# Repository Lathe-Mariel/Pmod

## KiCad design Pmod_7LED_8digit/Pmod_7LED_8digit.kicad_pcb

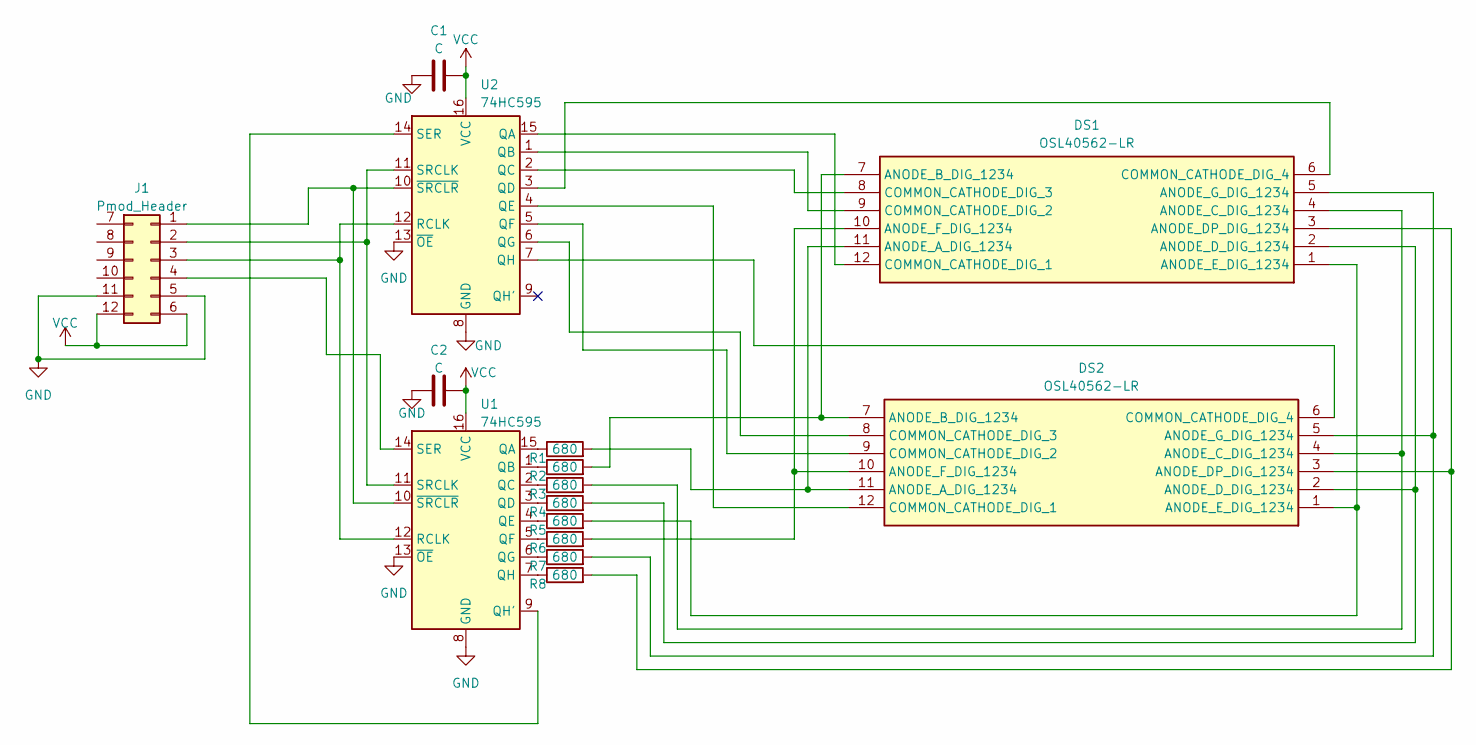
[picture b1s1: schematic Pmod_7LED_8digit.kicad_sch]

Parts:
C1: C; C_0603_1608Metric_Pad1.08x0.95mm_HandSolder
C2: C
DS1, DS2: OSL40562-LR; DIPS1524W50P254L5030H825Q12N; Manufacturer_Part_Number OSL40562-LR
J1: Pmod_Header
R1, R2, R3, R4, R5, R6, R7, R8: 680; R_0603_1608Metric_Pad0.98x0.95mm_HandSolder
U1, U2: 74HC595; SOIC-16W_5.3x10.2mm_P1.27mm

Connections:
GND: C1.2, C2.1, J1.5, J1.11, U1.8 (GND), U1.13 (~OE), U2.8 (GND), U2.13 (~OE)
unnamed: DS1.11 (ANODE_A_DIG_1234), DS2.11 (ANODE_A_DIG_1234), R1.2
unnamed: DS1.7 (ANODE_B_DIG_1234), DS2.7 (ANODE_B_DIG_1234), R2.2
unnamed: DS1.4 (ANODE_C_DIG_1234), DS2.4 (ANODE_C_DIG_1234), R3.2
unnamed: DS1.3 (ANODE_DP_DIG_1234), DS2.3 (ANODE_DP_DIG_1234), R8.2
unnamed: DS1.2 (ANODE_D_DIG_1234), DS2.2 (ANODE_D_DIG_1234), R4.2
unnamed: DS1.1 (ANODE_E_DIG_1234), DS2.1 (ANODE_E_DIG_1234), R5.2
unnamed: DS1.10 (ANODE_F_DIG_1234), DS2.10 (ANODE_F_DIG_1234), R6.2
unnamed: DS1.5 (ANODE_G_DIG_1234), DS2.5 (ANODE_G_DIG_1234), R7.2
unnamed: DS1.12 (COMMON_CATHODE_DIG_1), U2.15 (QA)
unnamed: DS1.9 (COMMON_CATHODE_DIG_2), U2.1 (QB)
unnamed: DS1.8 (COMMON_CATHODE_DIG_3), U2.2 (QC)
unnamed: DS1.6 (COMMON_CATHODE_DIG_4), U2.3 (QD)
unnamed: DS2.12 (COMMON_CATHODE_DIG_1), U2.4 (QE)
unnamed: DS2.9 (COMMON_CATHODE_DIG_2), U2.5 (QF)
unnamed: DS2.8 (COMMON_CATHODE_DIG_3), U2.6 (QG)
unnamed: DS2.6 (COMMON_CATHODE_DIG_4), U2.7 (QH)
unnamed: J1.1, U1.10 (~SRCLR), U2.10 (~SRCLR)
unnamed: J1.2, U1.11 (SRCLK), U2.11 (SRCLK)
unnamed: J1.3, U1.12 (RCLK), U2.12 (RCLK)
unnamed: J1.4, U1.14 (SER)
unnamed: R1.1, U1.15 (QA)
unnamed: R2.1, U1.1 (QB)
unnamed: R3.1, U1.2 (QC)
unnamed: R4.1, U1.3 (QD)
unnamed: R5.1, U1.4 (QE)
unnamed: R6.1, U1.5 (QF)
unnamed: R7.1, U1.6 (QG)
unnamed: U1.9 (QH'), U2.14 (SER)
unnamed: R8.1, U1.7 (QH)
VCC: C1.1, C2.2, J1.6, J1.12, U1.16 (VCC), U2.16 (VCC)

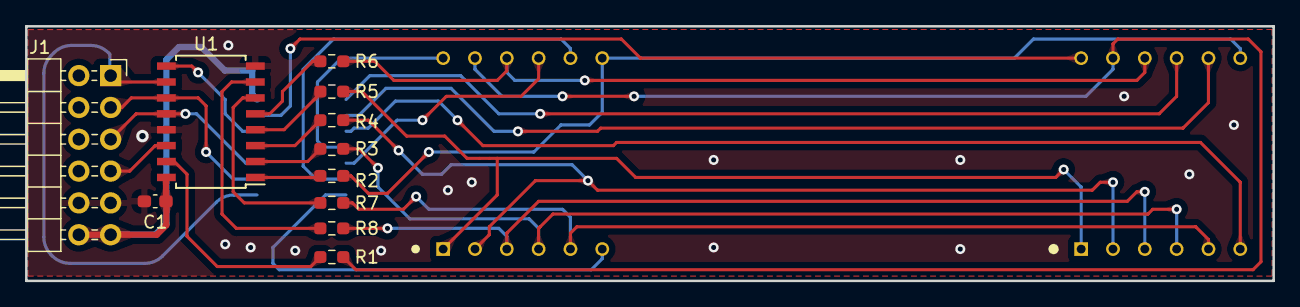
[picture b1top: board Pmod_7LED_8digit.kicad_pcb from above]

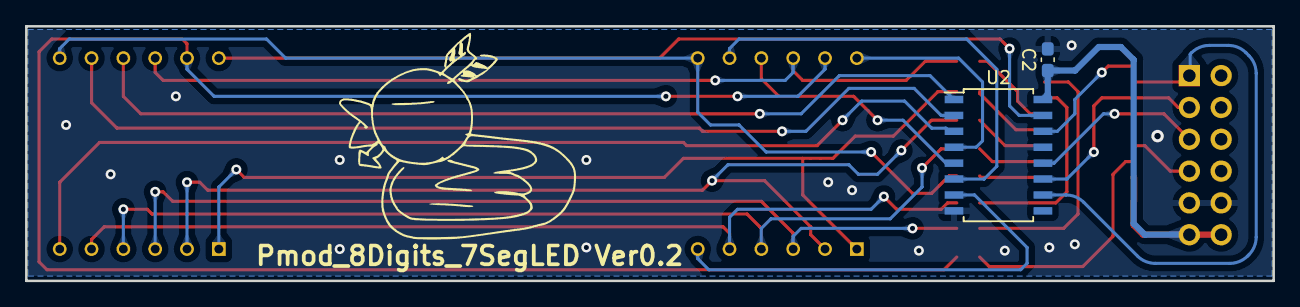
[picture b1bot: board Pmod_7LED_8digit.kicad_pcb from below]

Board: 2 copper layers, 99.6 x 20.3 mm, 15 parts (2 on the bottom side), 31 nets.

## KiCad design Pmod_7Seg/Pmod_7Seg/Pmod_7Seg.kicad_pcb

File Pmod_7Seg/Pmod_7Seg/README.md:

# Pmod_7Seg
6桁7セグLEDを載せたPmod基板．  
Pmodを2ポート使う  

2個取りした面付けデータがkikitディレクトリにあります．

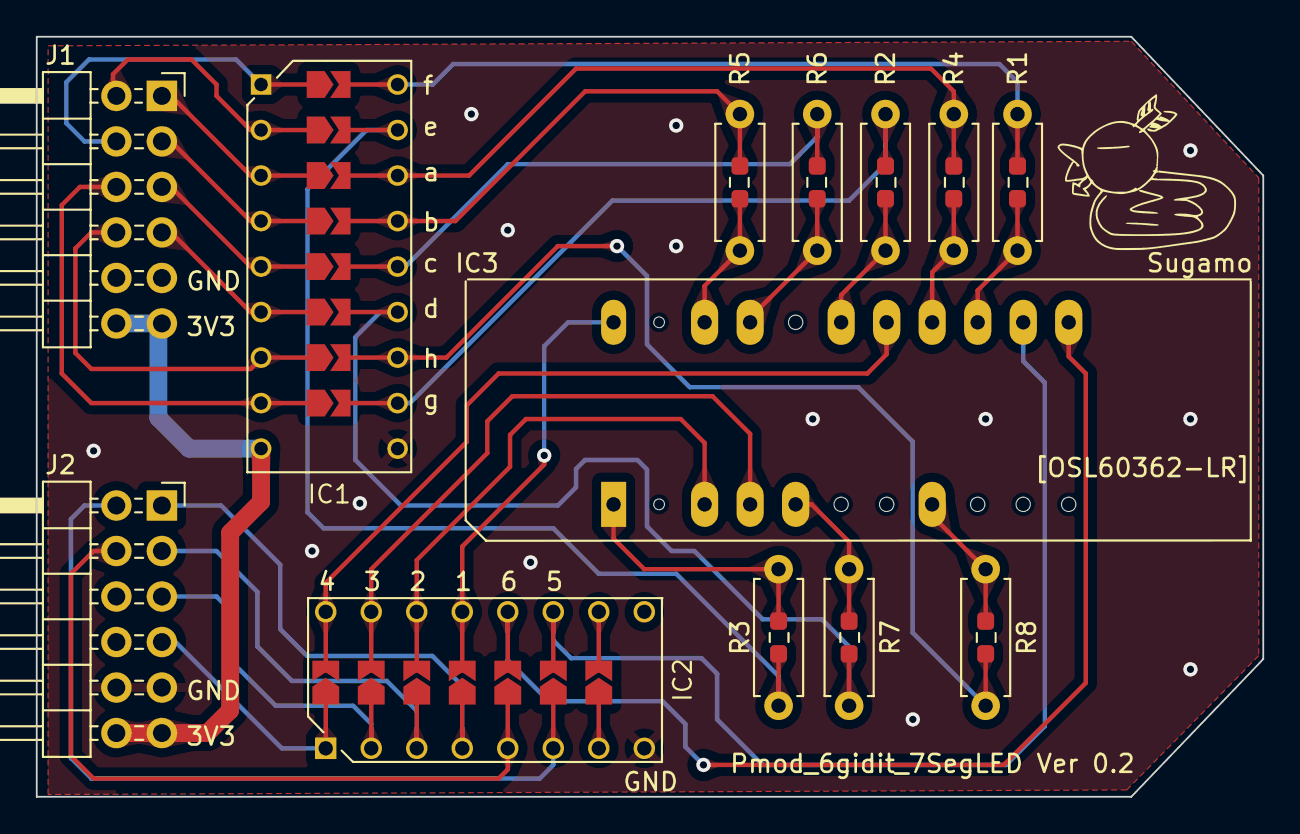
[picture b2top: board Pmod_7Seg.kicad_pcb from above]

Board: 2 copper layers, 68.5 x 42.4 mm, 13 parts (0 on the bottom side), 38 nets.

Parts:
IC1: TBD62783APG; DIP762W55P254L2286H480Q18N_with_solderjumper
IC2: TBD62003APG; DIP762W60P254L1975H445Q16N_solderjumper
IC3: OSL60362-LR; OSL60362-LR-with-allpin
J1, J2: Conn_02x06_Counter_Clockwise; Pmod
R1, R2, R3, R4, R5, R6, R7, R8: 68; Resistor_SMD_THT

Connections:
GND: IC1.10 (GND), IC2.8 (GND), J1.5, J1.11, J2.5, J2.11
unnamed: IC3.15 (ANODE_A), R4.1
unnamed: IC3.20 (ANODE_B), R5.2
unnamed: IC3.19 (ANODE_C), R6.2
unnamed: IC3.5 (ANODE_D), R7.2
unnamed: IC3.8 (ANODE_DP), R8.2
unnamed: IC3.1 (ANODE_E), R3.2
unnamed: IC3.14 (ANODE_F), R1.1
unnamed: IC3.17 (ANODE_G), R2.1
unnamed: IC2.13 (O4), IC3.22 (KATHODE_1)
unnamed: IC2.14 (O3), IC3.3 (KATHODE_2)
unnamed: IC2.15 (O2), IC3.4 (KATHODE_3)
unnamed: IC2.16 (O1), IC3.16 (KATHODE_4)
unnamed: IC2.11 (O6), IC3.13 (KATHODE_5)
unnamed: IC2.12 (O5), IC3.12 (KATHODE_6)
unnamed: IC1.1 (I1), J1.8
unnamed: IC1.2 (I2), J1.7
unnamed: IC1.3 (I3), J1.1
unnamed: IC1.4 (I4), J1.2
unnamed: IC1.5 (I5), J1.3
unnamed: IC1.6 (I6), J1.4
unnamed: IC1.7 (I7), J1.10
unnamed: IC1.8 (I8), J1.9
unnamed: IC1.18 (O1), R1.2
unnamed: IC1.17 (O2), R3.1
unnamed: IC1.16 (O3), R4.2
unnamed: IC1.15 (O4), R5.1
unnamed: IC1.14 (O5), R6.1
unnamed: IC1.13 (O6), R7.1
unnamed: IC1.12 (O7), R8.1
unnamed: IC1.11 (O8), R2.2
unnamed: IC2.4 (I4), J2.1
unnamed: IC2.3 (I3), J2.2
unnamed: IC2.2 (I2), J2.3
unnamed: IC2.1 (I1), J2.4
unnamed: IC2.6 (I6), J2.7
unnamed: IC2.5 (I5), J2.8
VCC: IC1.9 (VCC), J1.6, J1.12, J2.6, J2.12

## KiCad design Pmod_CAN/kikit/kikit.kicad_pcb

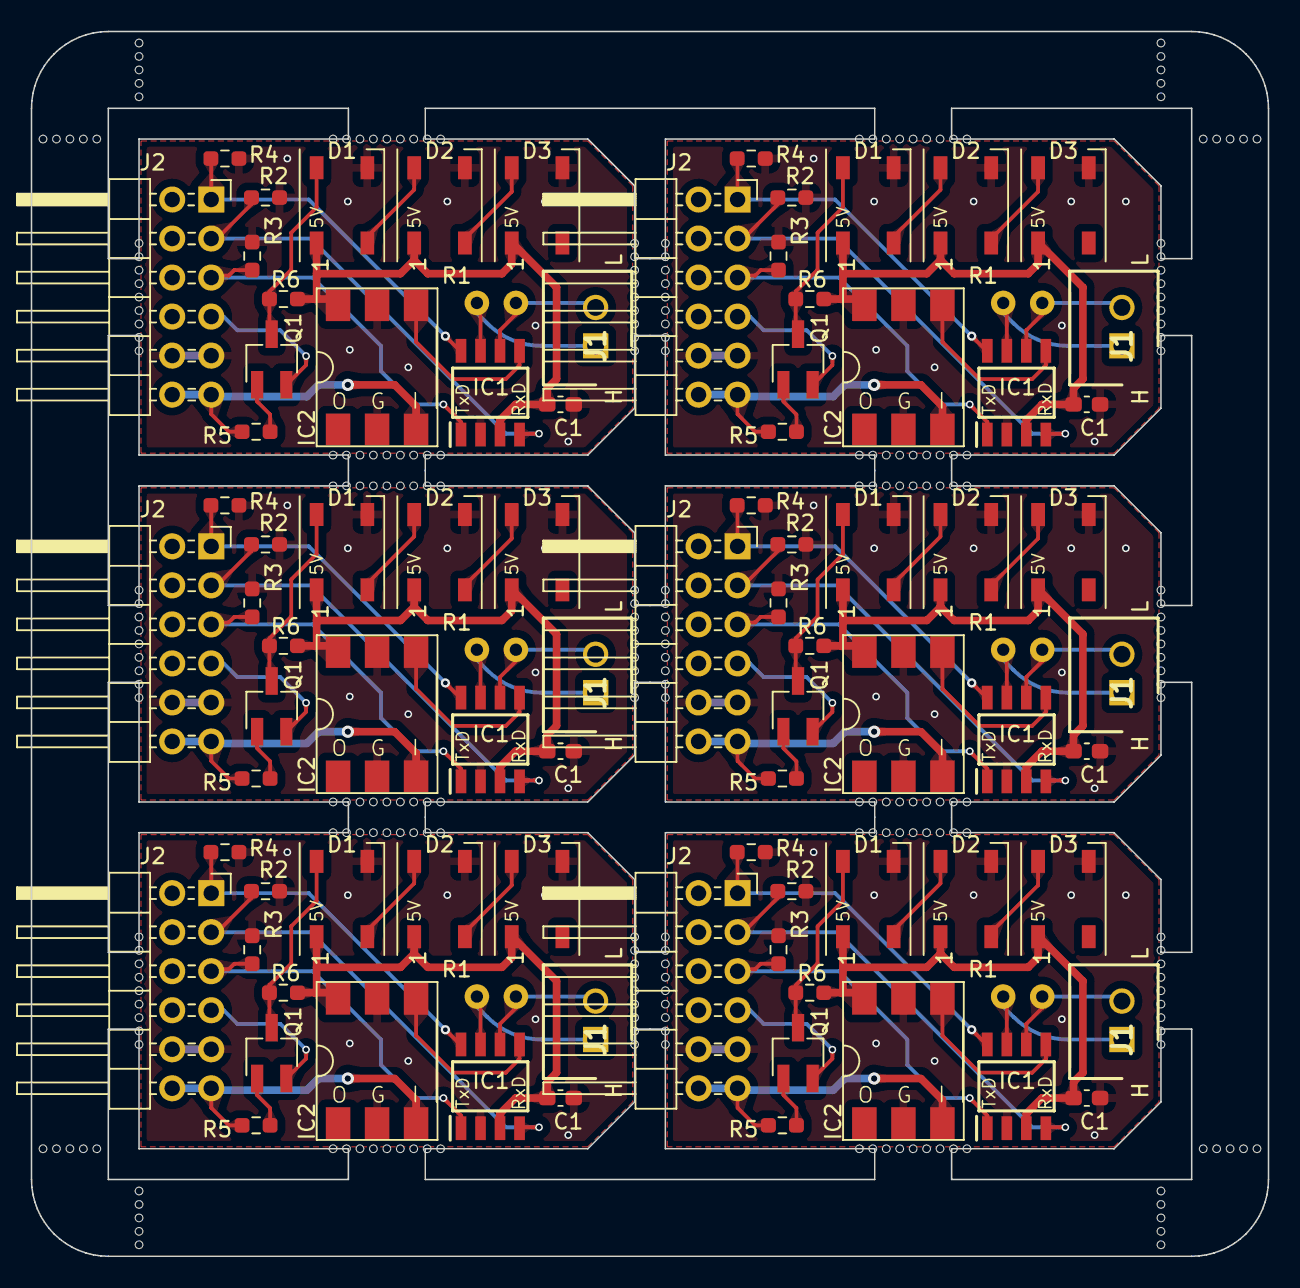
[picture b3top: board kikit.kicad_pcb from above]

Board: 2 copper layers, 80.5 x 79.7 mm, 346 parts (0 on the bottom side), 78 nets.

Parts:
C1, C1#2, C1#3, C1#4, C1#5, C1#6: 0.1u; C_0603_1608Metric_Pad1.08x0.95mm_HandSolder
D1, D1#2, D1#3, D1#4, D1#5, D1#6, D2, D2#2, D2#3, D2#4, D2#5, D2#6, D3, D3#2, D3#3, D3#4, D3#5, D3#6: WS2812B; LED_WS2812B_PLCC4_5.0x5.0mm_P3.2mm
IC1, IC1#2, IC1#3, IC1#4, IC1#5, IC1#6: TJA1441AT; SOIC127P600X175-8N
IC2, IC2#2, IC2#3, IC2#4, IC2#5, IC2#6: AE_XC9306-5V0; AE-XC9306-5V0
J1, J1#2, J1#3, J1#4, J1#5, J1#6: B2B-XH-A_LF__SN_; SHDR2W64P0X250_1X2_740X575X700P
J2, J2#2, J2#3, J2#4, J2#5, J2#6: Pmod_Header; Pmod
KiKit_MB_1_1, KiKit_MB_1_2, KiKit_MB_1_3, KiKit_MB_1_4, KiKit_MB_1_5, KiKit_MB_1_6, KiKit_MB_1_7, KiKit_MB_1_8, KiKit_MB_1_9, KiKit_MB_2_1, KiKit_MB_2_2, KiKit_MB_2_3, KiKit_MB_2_4, KiKit_MB_2_5, KiKit_MB_2_6, KiKit_MB_2_7, KiKit_MB_2_8, KiKit_MB_2_9, KiKit_MB_3_1, KiKit_MB_3_2, KiKit_MB_3_3, KiKit_MB_3_4, KiKit_MB_3_5, KiKit_MB_3_6, KiKit_MB_3_7, KiKit_MB_3_8, KiKit_MB_3_9, KiKit_MB_4_1, KiKit_MB_4_2, KiKit_MB_4_3, KiKit_MB_4_4, KiKit_MB_4_5, KiKit_MB_4_6, KiKit_MB_4_7, KiKit_MB_4_8, KiKit_MB_4_9, KiKit_MB_5_1, KiKit_MB_5_2, KiKit_MB_5_3, KiKit_MB_5_4, KiKit_MB_5_5, KiKit_MB_5_6, KiKit_MB_5_7, KiKit_MB_5_8, KiKit_MB_5_9, KiKit_MB_6_1, KiKit_MB_6_2, KiKit_MB_6_3, KiKit_MB_6_4, KiKit_MB_6_5, KiKit_MB_6_6, KiKit_MB_6_7, KiKit_MB_6_8, KiKit_MB_6_9, KiKit_MB_7_1, KiKit_MB_7_2, KiKit_MB_7_3, KiKit_MB_7_4, KiKit_MB_7_5, KiKit_MB_7_6, KiKit_MB_7_7, KiKit_MB_7_8, KiKit_MB_7_9, KiKit_MB_8_1, KiKit_MB_8_2, KiKit_MB_8_3, KiKit_MB_8_4, KiKit_MB_8_5, KiKit_MB_8_6, KiKit_MB_8_7, KiKit_MB_8_8, KiKit_MB_8_9, KiKit_MB_9_1, KiKit_MB_9_2, KiKit_MB_9_3, KiKit_MB_9_4, KiKit_MB_9_5, KiKit_MB_9_6, KiKit_MB_9_7, KiKit_MB_9_8, KiKit_MB_9_9, KiKit_MB_10_1, KiKit_MB_10_2, KiKit_MB_10_3, KiKit_MB_10_4, KiKit_MB_10_5, KiKit_MB_10_6, KiKit_MB_10_7, KiKit_MB_10_8, KiKit_MB_10_9, KiKit_MB_11_1, KiKit_MB_11_2, KiKit_MB_11_3, KiKit_MB_11_4, KiKit_MB_11_5, KiKit_MB_11_6, KiKit_MB_11_7, KiKit_MB_11_8, KiKit_MB_11_9, KiKit_MB_12_1, KiKit_MB_12_2, KiKit_MB_12_3, KiKit_MB_12_4, KiKit_MB_12_5, KiKit_MB_12_6, KiKit_MB_12_7, KiKit_MB_12_8, KiKit_MB_12_9, KiKit_MB_13_1, KiKit_MB_13_2, KiKit_MB_13_3, KiKit_MB_13_4, KiKit_MB_13_5, KiKit_MB_13_6, KiKit_MB_13_7, KiKit_MB_13_8, KiKit_MB_13_9, KiKit_MB_14_1, KiKit_MB_14_2, KiKit_MB_14_3, KiKit_MB_14_4, KiKit_MB_14_5, KiKit_MB_14_6, KiKit_MB_14_7, KiKit_MB_14_8, KiKit_MB_14_9, KiKit_MB_15_1, KiKit_MB_15_2, KiKit_MB_15_3, KiKit_MB_15_4, KiKit_MB_15_5, KiKit_MB_15_6, KiKit_MB_15_7, KiKit_MB_15_8, KiKit_MB_15_9, KiKit_MB_16_1, KiKit_MB_16_2, KiKit_MB_16_3, KiKit_MB_16_4, KiKit_MB_16_5, KiKit_MB_16_6, KiKit_MB_16_7, KiKit_MB_16_8, KiKit_MB_16_9, KiKit_MB_17_1, KiKit_MB_17_2, KiKit_MB_17_3, KiKit_MB_17_4, KiKit_MB_17_5, KiKit_MB_17_6, KiKit_MB_17_7, KiKit_MB_17_8, KiKit_MB_17_9, KiKit_MB_18_1, KiKit_MB_18_2, KiKit_MB_18_3, KiKit_MB_18_4, KiKit_MB_18_5, KiKit_MB_18_6, KiKit_MB_18_7, KiKit_MB_18_8, KiKit_MB_18_9, KiKit_MB_19_1, KiKit_MB_19_2, KiKit_MB_19_3, KiKit_MB_19_4, KiKit_MB_19_5, KiKit_MB_19_6, KiKit_MB_19_7, KiKit_MB_19_8, KiKit_MB_19_9, KiKit_MB_20_1, KiKit_MB_20_2, KiKit_MB_20_3, KiKit_MB_20_4, KiKit_MB_20_5, KiKit_MB_20_6, KiKit_MB_20_7, KiKit_MB_20_8, KiKit_MB_20_9, KiKit_MB_21_1, KiKit_MB_21_2, KiKit_MB_21_3, KiKit_MB_21_4, KiKit_MB_21_5, KiKit_MB_21_6, KiKit_MB_21_7, KiKit_MB_21_8, KiKit_MB_21_9, KiKit_MB_22_1, KiKit_MB_22_2, KiKit_MB_22_3, KiKit_MB_22_4, KiKit_MB_22_5, KiKit_MB_22_6, KiKit_MB_22_7, KiKit_MB_22_8, KiKit_MB_22_9, KiKit_MB_23_1, KiKit_MB_23_2, KiKit_MB_23_3, KiKit_MB_23_4, KiKit_MB_23_5, KiKit_MB_23_6, KiKit_MB_23_7, KiKit_MB_23_8, KiKit_MB_23_9, KiKit_MB_24_1, KiKit_MB_24_2, KiKit_MB_24_3, KiKit_MB_24_4, KiKit_MB_24_5, KiKit_MB_24_6, KiKit_MB_24_7, KiKit_MB_24_8, KiKit_MB_24_9, KiKit_MB_25_3, KiKit_MB_25_4, KiKit_MB_25_5, KiKit_MB_25_6, KiKit_MB_25_7, KiKit_MB_26_3, KiKit_MB_26_4, KiKit_MB_26_5, KiKit_MB_26_6, KiKit_MB_26_7, KiKit_MB_27_3, KiKit_MB_27_4, KiKit_MB_27_5, KiKit_MB_27_6, KiKit_MB_27_7, KiKit_MB_28_3, KiKit_MB_28_4, KiKit_MB_28_5, KiKit_MB_28_6, KiKit_MB_28_7, KiKit_MB_29_3, KiKit_MB_29_4, KiKit_MB_29_5, KiKit_MB_29_6, KiKit_MB_29_7, KiKit_MB_30_3, KiKit_MB_30_4, KiKit_MB_30_5, KiKit_MB_30_6, KiKit_MB_30_7, KiKit_MB_31_3, KiKit_MB_31_4, KiKit_MB_31_5, KiKit_MB_31_6, KiKit_MB_31_7, KiKit_MB_32_3, KiKit_MB_32_4, KiKit_MB_32_5, KiKit_MB_32_6, KiKit_MB_32_7: NPTH
Q1, Q1#2, Q1#3, Q1#4, Q1#5, Q1#6: Q_NPN_BEC; SC-59_Handsoldering
R1, R1#2, R1#3, R1#4, R1#5, R1#6: 120; R_Axial_DIN0309_L9.0mm_D3.2mm_P2.54mm_Vertical
R2, R2#2, R2#3, R2#4, R2#5, R2#6, R3, R3#2, R3#3, R3#4, R3#5, R3#6, R4, R4#2, R4#3, R4#4, R4#5, R4#6: R; R_0603_1608Metric_Pad0.98x0.95mm_HandSolder
R5, R5#2, R5#3, R5#4, R5#5, R5#6: 4.7k; R_0603_1608Metric_Pad0.98x0.95mm_HandSolder
R6, R6#2, R6#3, R6#4, R6#5, R6#6: 10k; R_0603_1608Metric_Pad0.98x0.95mm_HandSolder

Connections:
Board_0-+3V3: IC1#6.5 (VIO), IC2#3.3, J2.6, J2.12, R5#3.1
Board_0-/+5V: C1#6.2, D1#4.1 (VDD), D2#3.1 (VDD), D3#6.1 (VDD), IC1#6.3 (VCC), IC2#3.1, R6#3.2
Board_0-GND: C1#6.1, D1#4.3 (VSS), D2#3.3 (VSS), D3#6.3 (VSS), IC1#6.2 (GND), IC2#3.2 (G), J2.5, J2.11, R2#6.2, R3#4.2, R4#4.2
Board_0-Net-(D1-DIN): D1#4.4 (DIN), Q1#3.3 (C), R6#3.1
Board_0-Net-(D1-DOUT): D1#4.2 (DOUT), D2#3.4 (DIN)
Board_0-Net-(D2-DOUT): D2#3.2 (DOUT), D3#6.4 (DIN)
Board_0-Net-(IC1-CANH): IC1#6.7 (CANH), J1#3.1, R1#2.1
Board_0-Net-(IC1-CANL): IC1#6.6 (CANL), J1#3.2, R1#2.2
Board_0-Net-(IC1-RXD): IC1#6.4 (RXD), J2.2, R2#6.1
Board_0-Net-(IC1-S): IC1#6.8 (S), J2.1, R4#4.1
Board_0-Net-(IC1-TXD): IC1#6.1 (TXD), J2.3, R3#4.1
Board_0-Net-(J2-Pin_4): J2.4, Q1#3.2 (E)
Board_0-Net-(Q1-B): Q1#3.1 (B), R5#3.2
Board_1-+3V3: IC1#3.5 (VIO), IC2.3, J2#4.6, J2#4.12, R5#4.1
Board_1-/+5V: C1#5.2, D1#3.1 (VDD), D2#2.1 (VDD), D3.1 (VDD), IC1#3.3 (VCC), IC2.1, R6.2
Board_1-GND: C1#5.1, D1#3.3 (VSS), D2#2.3 (VSS), D3.3 (VSS), IC1#3.2 (GND), IC2.2 (G), J2#4.5, J2#4.11, R2#5.2, R3.2, R4#5.2
Board_1-Net-(D1-DIN): D1#3.4 (DIN), Q1#4.3 (C), R6.1
Board_1-Net-(D1-DOUT): D1#3.2 (DOUT), D2#2.4 (DIN)
Board_1-Net-(D2-DOUT): D2#2.2 (DOUT), D3.4 (DIN)
Board_1-Net-(IC1-CANH): IC1#3.7 (CANH), J1#4.1, R1#4.1
Board_1-Net-(IC1-CANL): IC1#3.6 (CANL), J1#4.2, R1#4.2
Board_1-Net-(IC1-RXD): IC1#3.4 (RXD), J2#4.2, R2#5.1
Board_1-Net-(IC1-S): IC1#3.8 (S), J2#4.1, R4#5.1
Board_1-Net-(IC1-TXD): IC1#3.1 (TXD), J2#4.3, R3.1
Board_1-Net-(J2-Pin_4): J2#4.4, Q1#4.2 (E)
Board_1-Net-(Q1-B): Q1#4.1 (B), R5#4.2
Board_2-+3V3: IC1#5.5 (VIO), IC2#6.3, J2#6.6, J2#6.12, R5#5.1
Board_2-/+5V: C1.2, D1#6.1 (VDD), D2#5.1 (VDD), D3#4.1 (VDD), IC1#5.3 (VCC), IC2#6.1, R6#6.2
Board_2-GND: C1.1, D1#6.3 (VSS), D2#5.3 (VSS), D3#4.3 (VSS), IC1#5.2 (GND), IC2#6.2 (G), J2#6.5, J2#6.11, R2.2, R3#6.2, R4#2.2
Board_2-Net-(D1-DIN): D1#6.4 (DIN), Q1#2.3 (C), R6#6.1
Board_2-Net-(D1-DOUT): D1#6.2 (DOUT), D2#5.4 (DIN)
Board_2-Net-(D2-DOUT): D2#5.2 (DOUT), D3#4.4 (DIN)
Board_2-Net-(IC1-CANH): IC1#5.7 (CANH), J1.1, R1#5.1
Board_2-Net-(IC1-CANL): IC1#5.6 (CANL), J1.2, R1#5.2
Board_2-Net-(IC1-RXD): IC1#5.4 (RXD), J2#6.2, R2.1
Board_2-Net-(IC1-S): IC1#5.8 (S), J2#6.1, R4#2.1
Board_2-Net-(IC1-TXD): IC1#5.1 (TXD), J2#6.3, R3#6.1
Board_2-Net-(J2-Pin_4): J2#6.4, Q1#2.2 (E)
Board_2-Net-(Q1-B): Q1#2.1 (B), R5#5.2
Board_3-+3V3: IC1#4.5 (VIO), IC2#5.3, J2#5.6, J2#5.12, R5.1
Board_3-/+5V: C1#2.2, D1#5.1 (VDD), D2#4.1 (VDD), D3#5.1 (VDD), IC1#4.3 (VCC), IC2#5.1, R6#5.2
Board_3-GND: C1#2.1, D1#5.3 (VSS), D2#4.3 (VSS), D3#5.3 (VSS), IC1#4.2 (GND), IC2#5.2 (G), J2#5.5, J2#5.11, R2#3.2, R3#3.2, R4#6.2
Board_3-Net-(D1-DIN): D1#5.4 (DIN), Q1.3 (C), R6#5.1
Board_3-Net-(D1-DOUT): D1#5.2 (DOUT), D2#4.4 (DIN)
Board_3-Net-(D2-DOUT): D2#4.2 (DOUT), D3#5.4 (DIN)
Board_3-Net-(IC1-CANH): IC1#4.7 (CANH), J1#6.1, R1#6.1
Board_3-Net-(IC1-CANL): IC1#4.6 (CANL), J1#6.2, R1#6.2
Board_3-Net-(IC1-RXD): IC1#4.4 (RXD), J2#5.2, R2#3.1
Board_3-Net-(IC1-S): IC1#4.8 (S), J2#5.1, R4#6.1
Board_3-Net-(IC1-TXD): IC1#4.1 (TXD), J2#5.3, R3#3.1
Board_3-Net-(J2-Pin_4): J2#5.4, Q1.2 (E)
Board_3-Net-(Q1-B): Q1.1 (B), R5.2
Board_4-+3V3: IC1#2.5 (VIO), IC2#2.3, J2#3.6, J2#3.12, R5#6.1
Board_4-/+5V: C1#4.2, D1.1 (VDD), D2.1 (VDD), D3#2.1 (VDD), IC1#2.3 (VCC), IC2#2.1, R6#4.2
Board_4-GND: C1#4.1, D1.3 (VSS), D2.3 (VSS), D3#2.3 (VSS), IC1#2.2 (GND), IC2#2.2 (G), J2#3.5, J2#3.11, R2#4.2, R3#2.2, R4#3.2
Board_4-Net-(D1-DIN): D1.4 (DIN), Q1#5.3 (C), R6#4.1
Board_4-Net-(D1-DOUT): D1.2 (DOUT), D2.4 (DIN)
Board_4-Net-(D2-DOUT): D2.2 (DOUT), D3#2.4 (DIN)
Board_4-Net-(IC1-CANH): IC1#2.7 (CANH), J1#5.1, R1#3.1
Board_4-Net-(IC1-CANL): IC1#2.6 (CANL), J1#5.2, R1#3.2
Board_4-Net-(IC1-RXD): IC1#2.4 (RXD), J2#3.2, R2#4.1
Board_4-Net-(IC1-S): IC1#2.8 (S), J2#3.1, R4#3.1
Board_4-Net-(IC1-TXD): IC1#2.1 (TXD), J2#3.3, R3#2.1
Board_4-Net-(J2-Pin_4): J2#3.4, Q1#5.2 (E)
Board_4-Net-(Q1-B): Q1#5.1 (B), R5#6.2
Board_5-+3V3: IC1.5 (VIO), IC2#4.3, J2#2.6, J2#2.12, R5#2.1
Board_5-/+5V: C1#3.2, D1#2.1 (VDD), D2#6.1 (VDD), D3#3.1 (VDD), IC1.3 (VCC), IC2#4.1, R6#2.2
Board_5-GND: C1#3.1, D1#2.3 (VSS), D2#6.3 (VSS), D3#3.3 (VSS), IC1.2 (GND), IC2#4.2 (G), J2#2.5, J2#2.11, R2#2.2, R3#5.2, R4.2
Board_5-Net-(D1-DIN): D1#2.4 (DIN), Q1#6.3 (C), R6#2.1
Board_5-Net-(D1-DOUT): D1#2.2 (DOUT), D2#6.4 (DIN)
Board_5-Net-(D2-DOUT): D2#6.2 (DOUT), D3#3.4 (DIN)
Board_5-Net-(IC1-CANH): IC1.7 (CANH), J1#2.1, R1.1
Board_5-Net-(IC1-CANL): IC1.6 (CANL), J1#2.2, R1.2
Board_5-Net-(IC1-RXD): IC1.4 (RXD), J2#2.2, R2#2.1
Board_5-Net-(IC1-S): IC1.8 (S), J2#2.1, R4.1
Board_5-Net-(IC1-TXD): IC1.1 (TXD), J2#2.3, R3#5.1
Board_5-Net-(J2-Pin_4): J2#2.4, Q1#6.2 (E)
Board_5-Net-(Q1-B): Q1#6.1 (B), R5#2.2

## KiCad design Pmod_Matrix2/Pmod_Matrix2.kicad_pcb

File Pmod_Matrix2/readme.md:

# Pmod_MatrixLED2
KiCADで設計した，8×8　2色マトリクスLEDのモジュールです．  
コネクタのピン配置はPmod互換ですが，
基板の幅がPmodの規格に入っていないので，なんちゃってPmodです．

# Schematics

# BOM
アイテム（Item）|個数（Quantity）
---|---
74HC595 | 3
1608チップコンデンサ0.1μF capacitor | 3
1608チップ抵抗22Ω Register | 16
L型ダブルピンヘッダ（6列）L-2x6pinheader | 1
2色LEDMatrix LTP-12188M-08 | 1
ピンソケット 1x12 | 1（オプション）

# Repository
## output
Garber data made by KiCAD

## sample
Sample Design Project

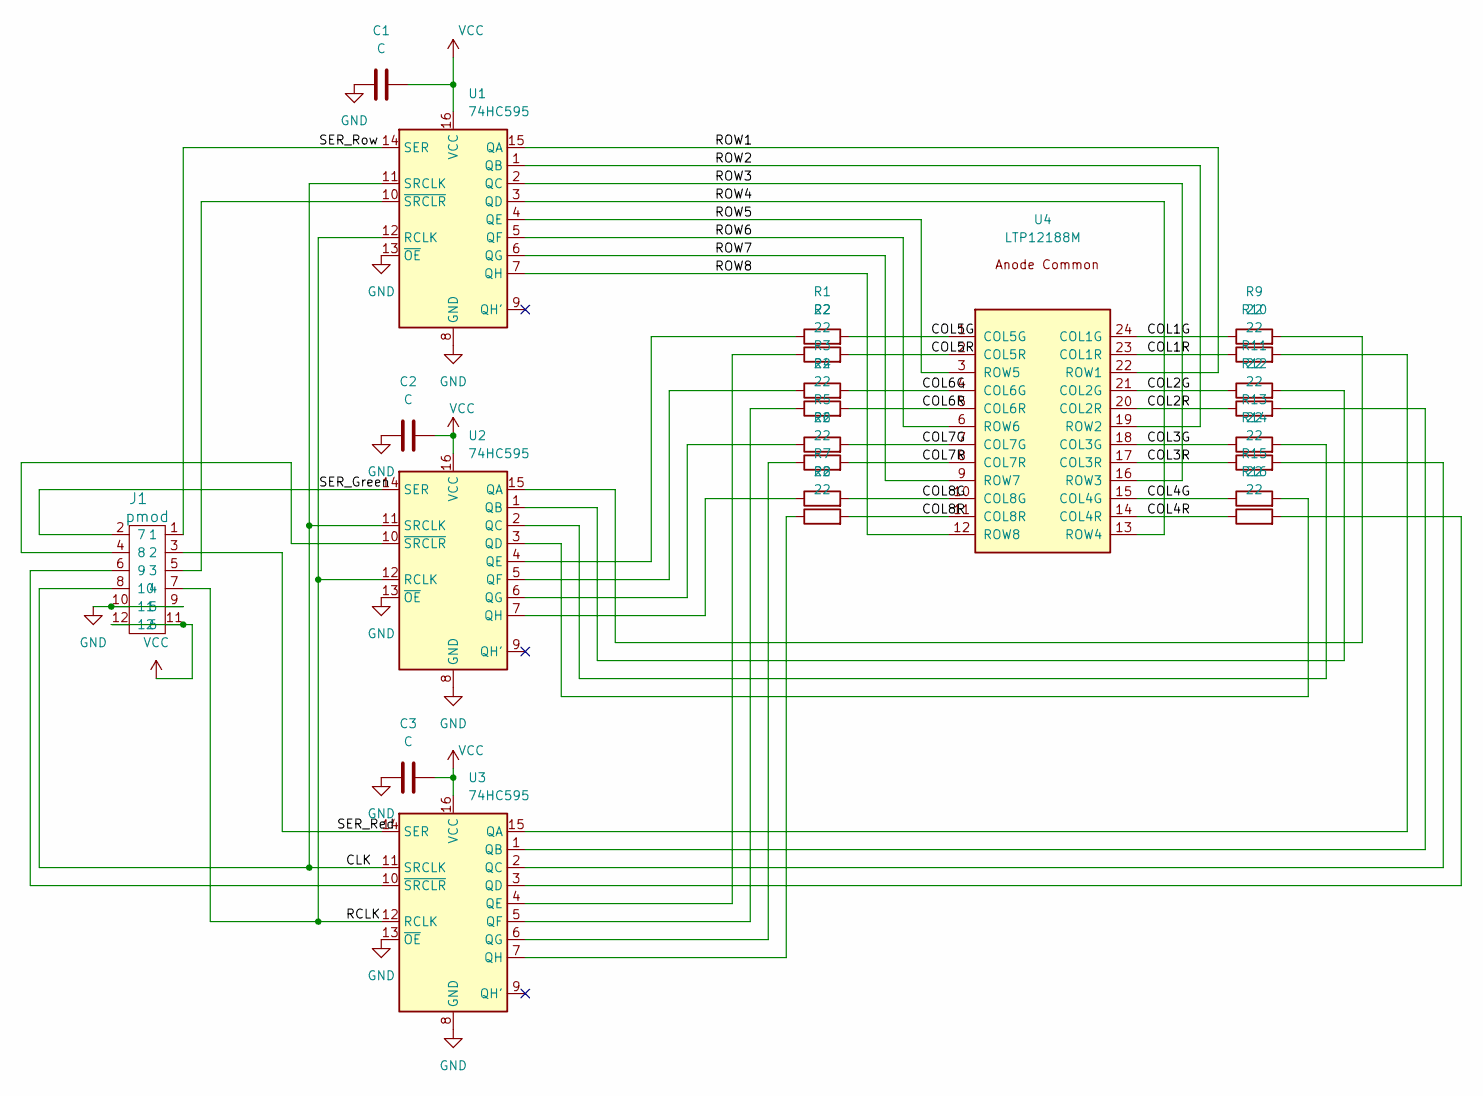
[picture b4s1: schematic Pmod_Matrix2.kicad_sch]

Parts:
C1, C2, C3: C; C_0603_1608Metric_Pad1.08x0.95mm_HandSolder
J1: pmod; PinHeader_2x06_P2.54mm_Horizontal; MPN 67996-412HLF; Digi-Key_PN 609-3219-ND
R1, R2, R3, R4, R5, R6, R7, R8, R9, R10, R11, R12, R13, R14, R15, R16: 22; R_0603_1608Metric_Pad0.98x0.95mm_HandSolder
U1, U2, U3: 74HC595; SOP-16_4.55x10.3mm_P1.27mm
U4: LTP12188M; LTP12188

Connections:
/CLK: J1.8 (10), U1.11 (SRCLK), U2.11 (SRCLK), U3.11 (SRCLK)
/COL1G: R9.1, U4.24 (COL1G)
/COL1R: R10.1, U4.23 (COL1R)
/COL2G: R11.1, U4.21 (COL2G)
/COL2R: R12.1, U4.20 (COL2R)
/COL3G: R13.1, U4.18 (COL3G)
/COL3R: R14.1, U4.17 (COL3R)
/COL4G: R15.1, U4.15 (COL4G)
/COL4R: R16.1, U4.14 (COL4R)
/COL5G: R1.2, U4.1 (COL5G)
/COL5R: R2.2, U4.2 (COL5R)
/COL6G: R3.2, U4.4 (COL6G)
/COL6R: R4.2, U4.5 (COL6R)
/COL7G: R5.2, U4.7 (COL7G)
/COL7R: R6.2, U4.8 (COL7R)
/COL8G: R7.2, U4.10 (COL8G)
/COL8R: R8.2, U4.11 (COL8R)
/ROW1: U1.15 (QA), U4.22 (ROW1)
/ROW2: U1.1 (QB), U4.19 (ROW2)
/ROW3: U1.2 (QC), U4.16 (ROW3)
/ROW4: U1.3 (QD), U4.13 (ROW4)
/ROW5: U1.4 (QE), U4.3 (ROW5)
/ROW6: U1.5 (QF), U4.6 (ROW6)
/ROW7: U1.6 (QG), U4.9 (ROW7)
/ROW8: U1.7 (QH), U4.12 (ROW8)
/SER_Red: J1.3 (2), U3.14 (SER)
/SER_Row: J1.1, U1.14 (SER)
GND: C1.1, C2.1, C3.1, J1.9 (5), J1.10 (11), U1.8 (GND), U1.13 (~OE), U2.8 (GND), U2.13 (~OE), U3.8 (GND), U3.13 (~OE)
unnamed: J1.4 (8), U2.10 (~SRCLR)
unnamed: J1.5 (3), U1.10 (~SRCLR)
unnamed: J1.6 (9), U3.10 (~SRCLR)
unnamed: R1.1, U2.4 (QE)
unnamed: R2.1, U3.4 (QE)
unnamed: R3.1, U2.5 (QF)
unnamed: R4.1, U3.5 (QF)
unnamed: R5.1, U2.6 (QG)
unnamed: R6.1, U3.6 (QG)
unnamed: R7.1, U2.7 (QH)
unnamed: R8.1, U3.7 (QH)
unnamed: R9.2, U2.15 (QA)
unnamed: R10.2, U3.15 (QA)
unnamed: R11.2, U2.1 (QB)
unnamed: R12.2, U3.1 (QB)
unnamed: R13.2, U2.2 (QC)
unnamed: R14.2, U3.2 (QC)
unnamed: R15.2, U2.3 (QD)
unnamed: R16.2, U3.3 (QD)
VCC: C1.2, C2.2, C3.2, J1.11 (6), J1.12, U1.16 (VCC), U2.16 (VCC), U3.16 (VCC)

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
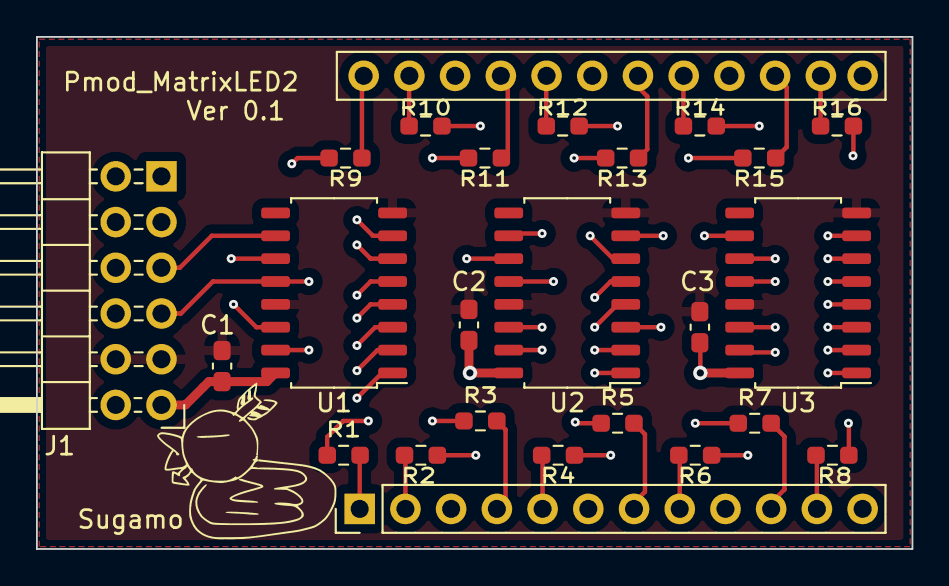
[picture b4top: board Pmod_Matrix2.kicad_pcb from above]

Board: 6 copper layers, 48.6 x 28.4 mm, 24 parts (0 on the bottom side), 50 nets.

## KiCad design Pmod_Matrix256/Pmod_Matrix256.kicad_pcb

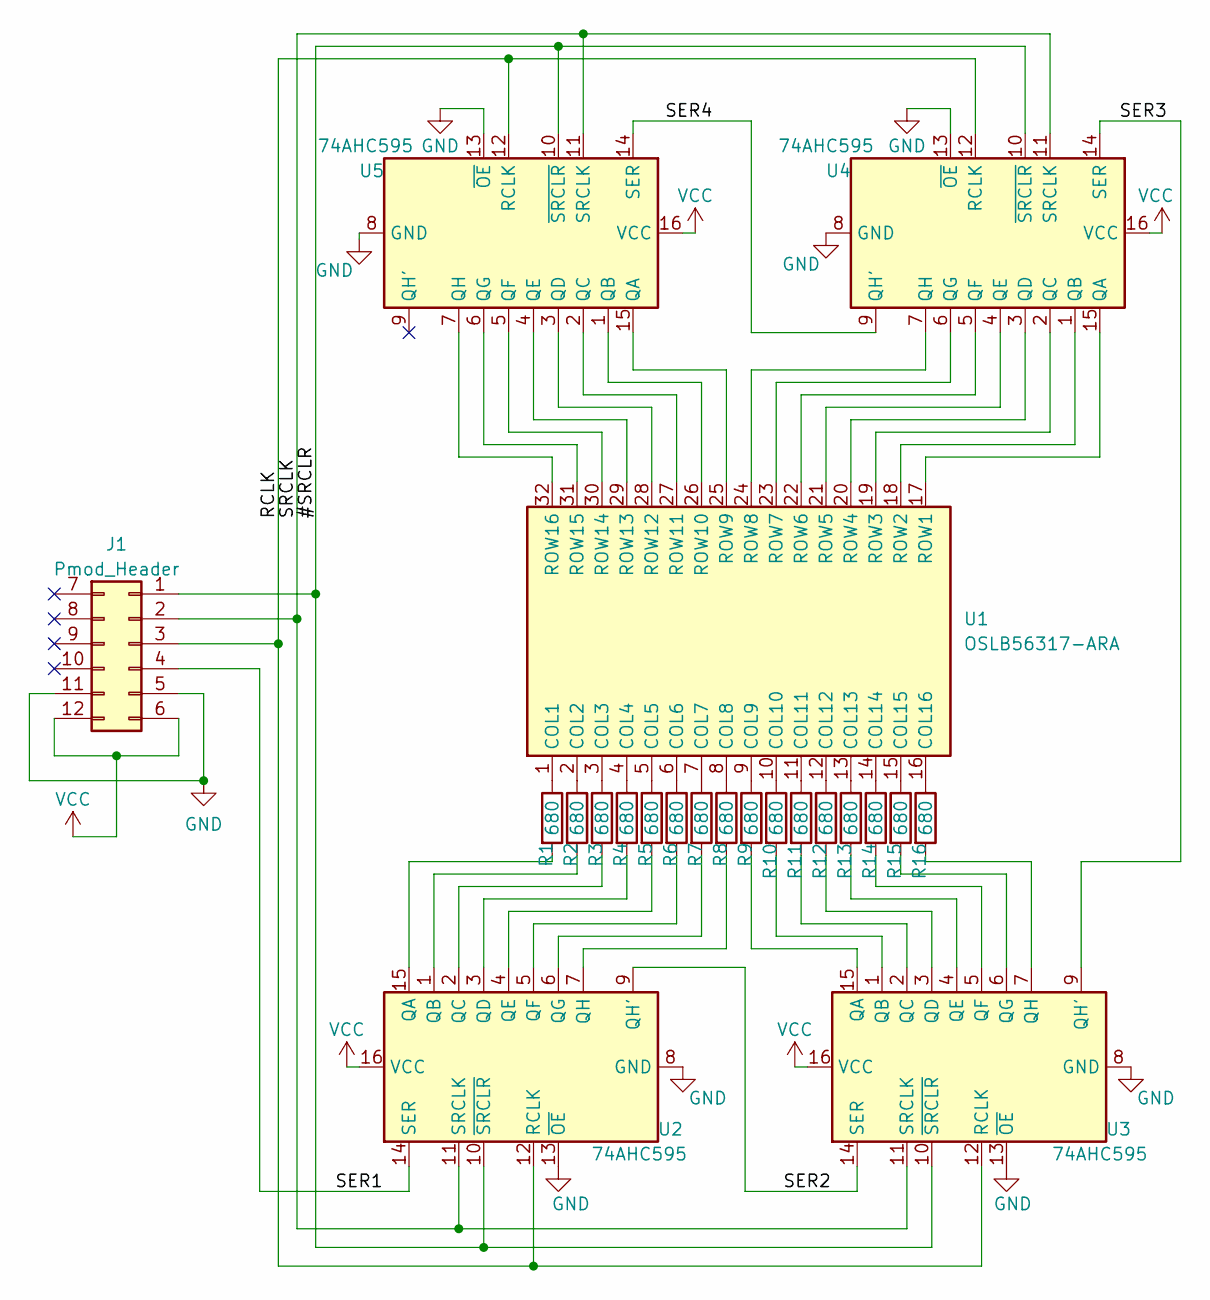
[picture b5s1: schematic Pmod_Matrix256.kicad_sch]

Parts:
J1: Pmod_Header; Pmod
R1, R2, R3, R4, R5, R6, R7, R8, R9, R10, R11, R12, R13, R14, R15, R16: 680; R_0603_1608Metric_Pad0.98x0.95mm_HandSolder
U1: OSLB56317-ARA
U2, U3, U4, U5: 74AHC595; SOIC-16_3.9x9.9mm_P1.27mm

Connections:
/#SRCLR: J1.1, U2.10 (~SRCLR), U3.10 (~SRCLR), U4.10 (~SRCLR), U5.10 (~SRCLR)
/RCLK: J1.3, U2.12 (RCLK), U3.12 (RCLK), U4.12 (RCLK), U5.12 (RCLK)
/SER1: J1.4, U2.14 (SER)
/SER2: U2.9 (QH'), U3.14 (SER)
/SER3: U3.9 (QH'), U4.14 (SER)
/SER4: U4.9 (QH'), U5.14 (SER)
/SRCLK: J1.2, U2.11 (SRCLK), U3.11 (SRCLK), U4.11 (SRCLK), U5.11 (SRCLK)
GND: J1.5, J1.11, U2.8 (GND), U2.13 (~OE), U3.8 (GND), U3.13 (~OE), U4.8 (GND), U4.13 (~OE), U5.8 (GND), U5.13 (~OE)
unnamed: R1.1, U1.1 (COL1)
unnamed: R2.1, U1.2 (COL2)
unnamed: R3.1, U1.3 (COL3)
unnamed: R4.1, U1.4 (COL4)
unnamed: R5.1, U1.5 (COL5)
unnamed: R6.1, U1.6 (COL6)
unnamed: R7.1, U1.7 (COL7)
unnamed: R8.1, U1.8 (COL8)
unnamed: R9.1, U1.9 (COL9)
unnamed: R10.1, U1.10 (COL10)
unnamed: R11.1, U1.11 (COL11)
unnamed: R12.1, U1.12 (COL12)
unnamed: R13.1, U1.13 (COL13)
unnamed: R14.1, U1.14 (COL14)
unnamed: R15.1, U1.15 (COL15)
unnamed: R16.1, U1.16 (COL16)
unnamed: U1.17 (ROW1), U4.15 (QA)
unnamed: U1.18 (ROW2), U4.1 (QB)
unnamed: U1.19 (ROW3), U4.2 (QC)
unnamed: U1.20 (ROW4), U4.3 (QD)
unnamed: U1.21 (ROW5), U4.4 (QE)
unnamed: U1.22 (ROW6), U4.5 (QF)
unnamed: U1.23 (ROW7), U4.6 (QG)
unnamed: U1.24 (ROW8), U4.7 (QH)
unnamed: U1.25 (ROW9), U5.15 (QA)
unnamed: U1.26 (ROW10), U5.1 (QB)
unnamed: U1.27 (ROW11), U5.2 (QC)
unnamed: U1.28 (ROW12), U5.3 (QD)
unnamed: U1.29 (ROW13), U5.4 (QE)
unnamed: U1.30 (ROW14), U5.5 (QF)
unnamed: U1.31 (ROW15), U5.6 (QG)
unnamed: U1.32 (ROW16), U5.7 (QH)
unnamed: R1.2, U2.15 (QA)
unnamed: R2.2, U2.1 (QB)
unnamed: R3.2, U2.2 (QC)
unnamed: R4.2, U2.3 (QD)
unnamed: R5.2, U2.4 (QE)
unnamed: R6.2, U2.5 (QF)
unnamed: R7.2, U2.6 (QG)
unnamed: R8.2, U2.7 (QH)
unnamed: R9.2, U3.15 (QA)
unnamed: R10.2, U3.1 (QB)
unnamed: R11.2, U3.2 (QC)
unnamed: R12.2, U3.3 (QD)
unnamed: R13.2, U3.4 (QE)
unnamed: R14.2, U3.5 (QF)
unnamed: R15.2, U3.6 (QG)
unnamed: R16.2, U3.7 (QH)
VCC: J1.6, J1.12, U2.16 (VCC), U3.16 (VCC), U4.16 (VCC), U5.16 (VCC)

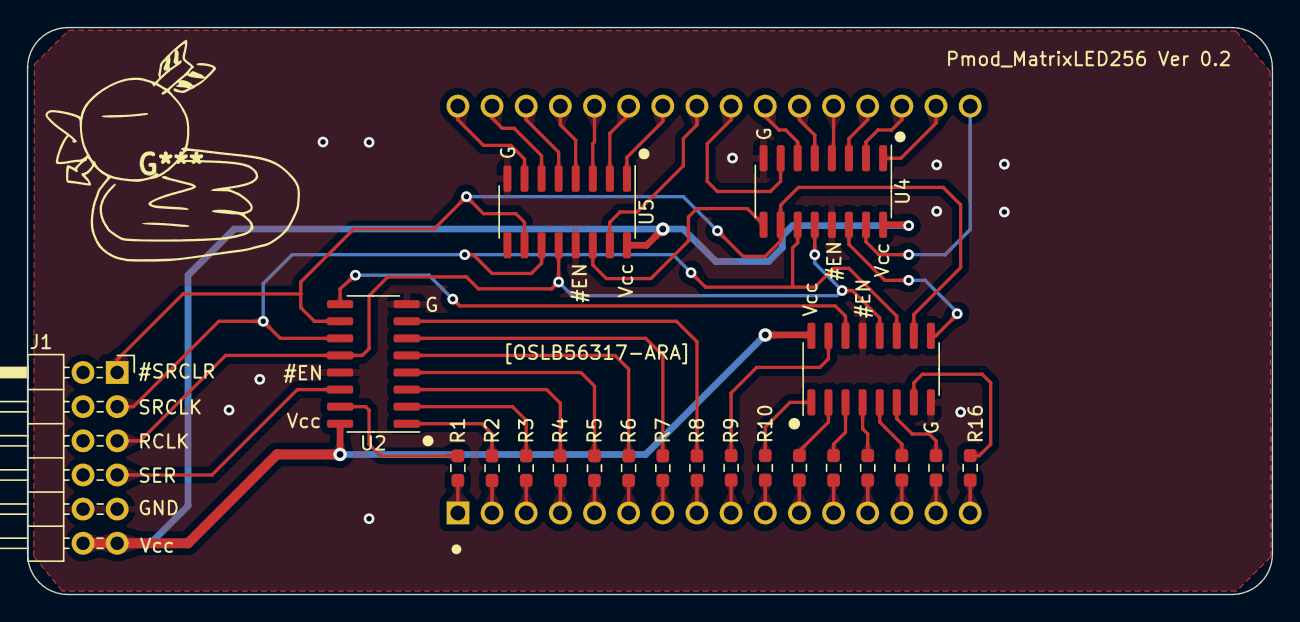
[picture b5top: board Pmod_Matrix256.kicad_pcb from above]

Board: 2 copper layers, 92.6 x 42.2 mm, 22 parts (0 on the bottom side), 57 nets.
